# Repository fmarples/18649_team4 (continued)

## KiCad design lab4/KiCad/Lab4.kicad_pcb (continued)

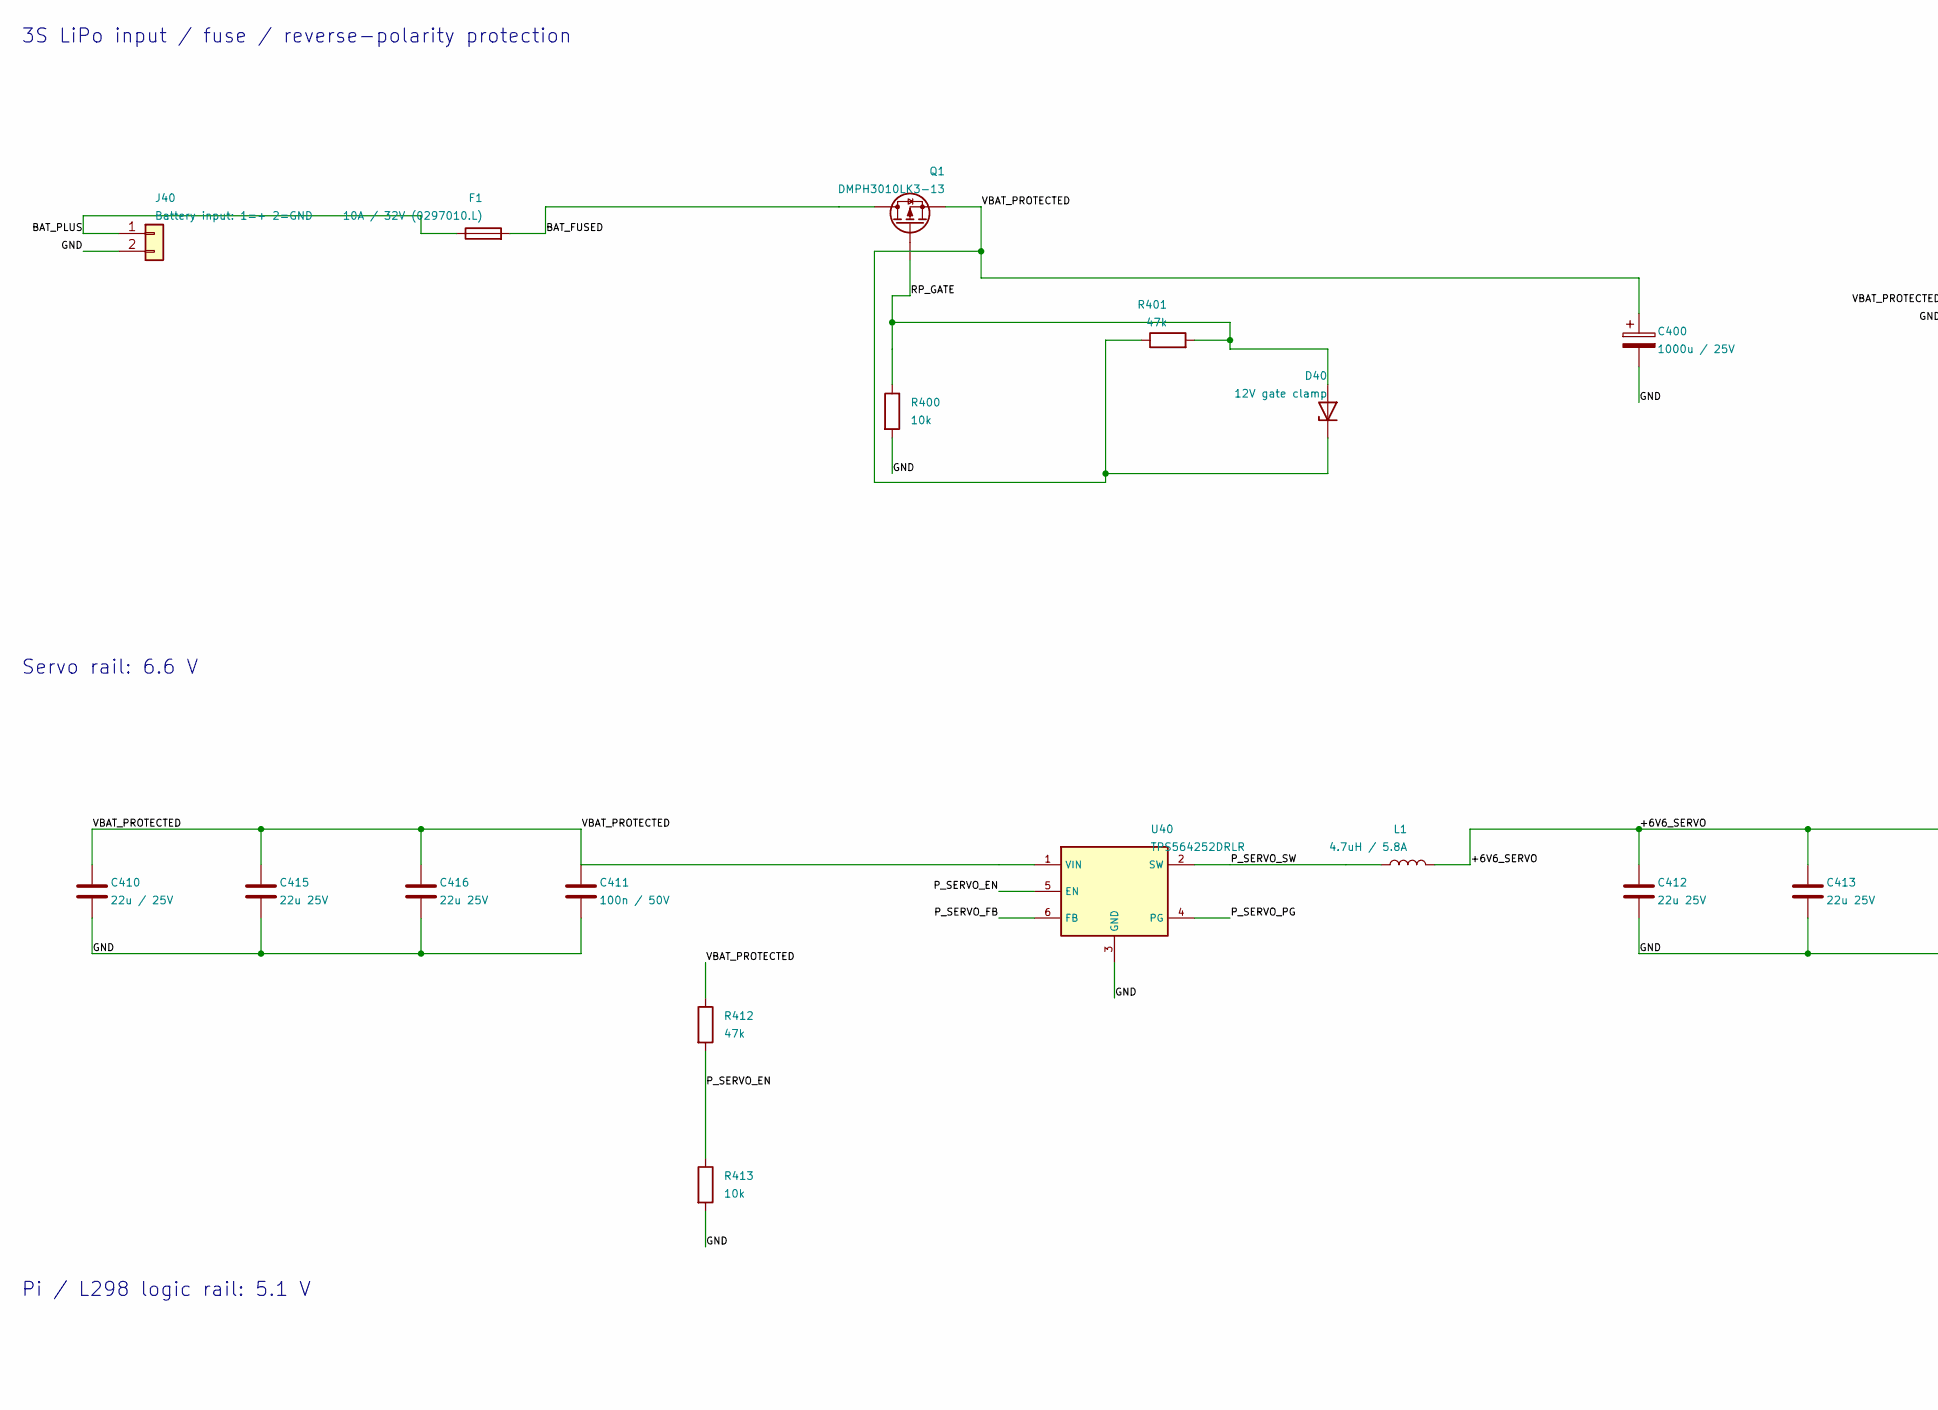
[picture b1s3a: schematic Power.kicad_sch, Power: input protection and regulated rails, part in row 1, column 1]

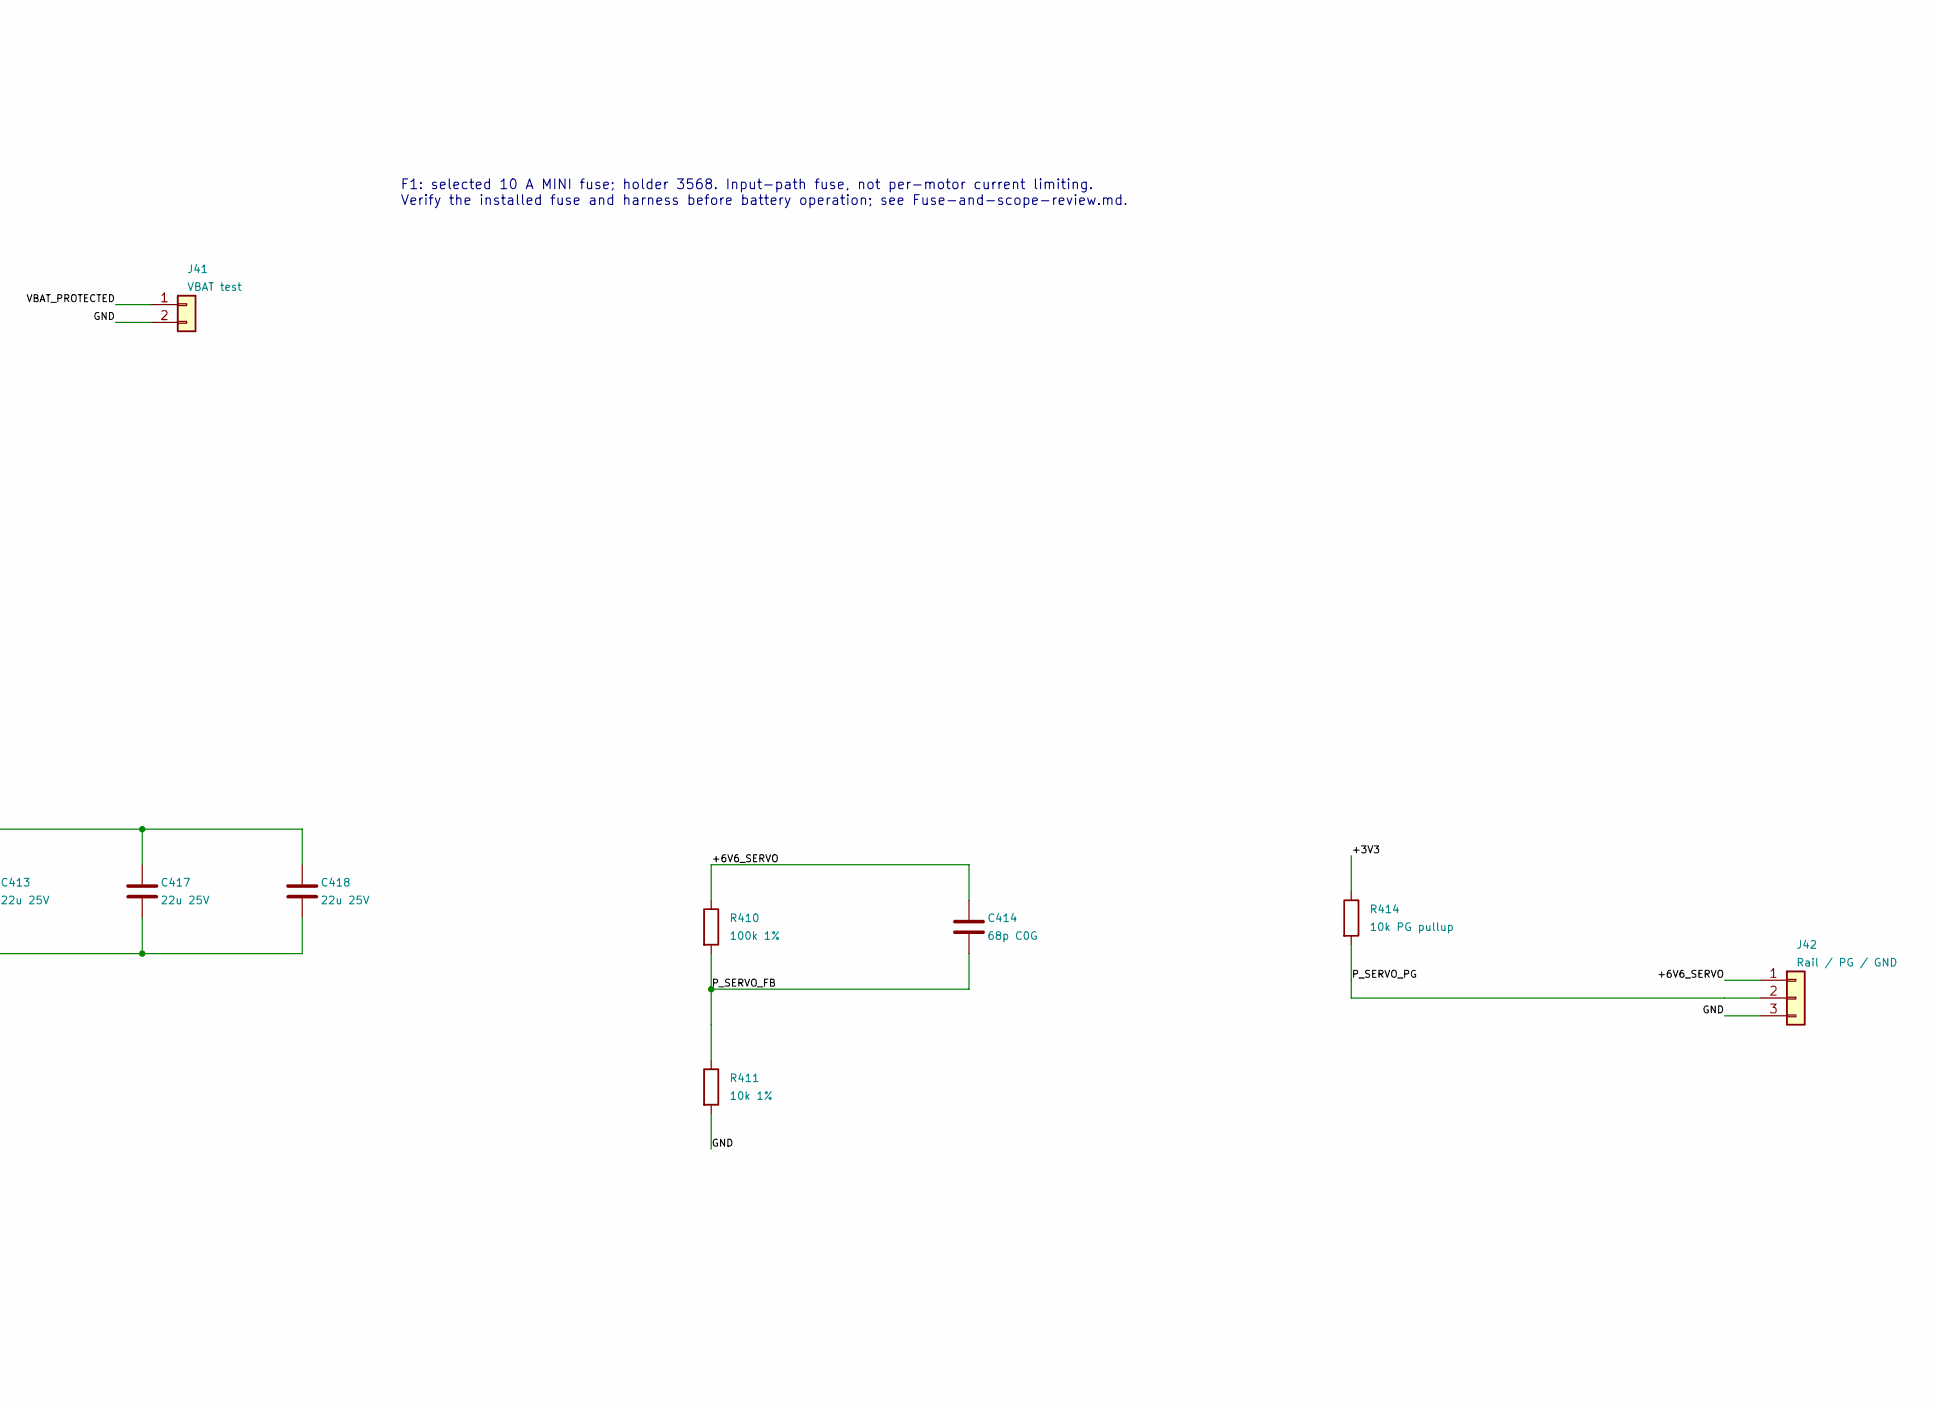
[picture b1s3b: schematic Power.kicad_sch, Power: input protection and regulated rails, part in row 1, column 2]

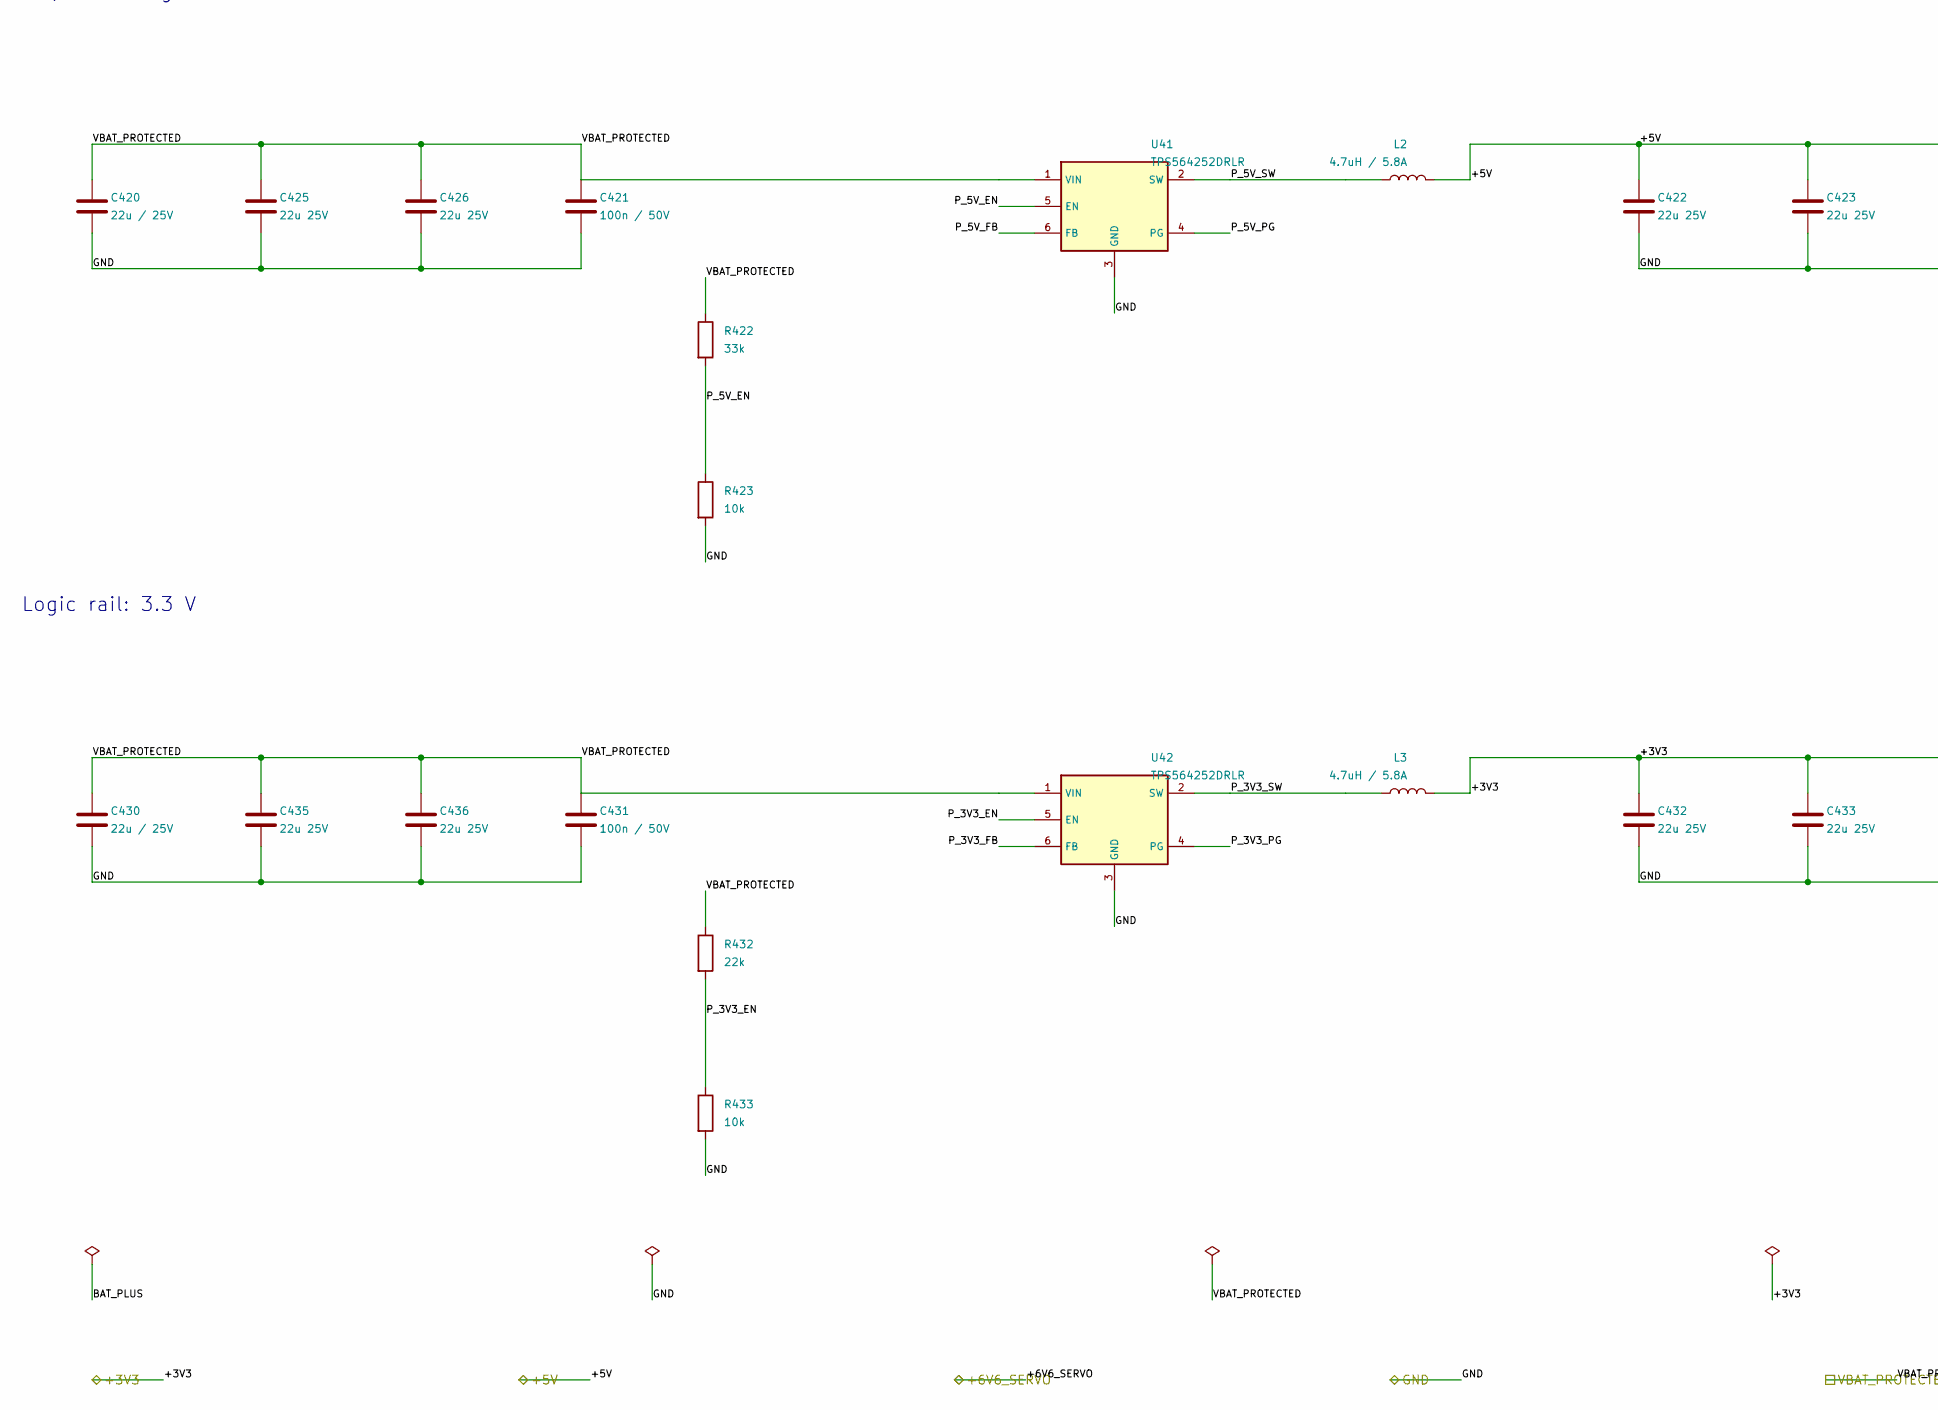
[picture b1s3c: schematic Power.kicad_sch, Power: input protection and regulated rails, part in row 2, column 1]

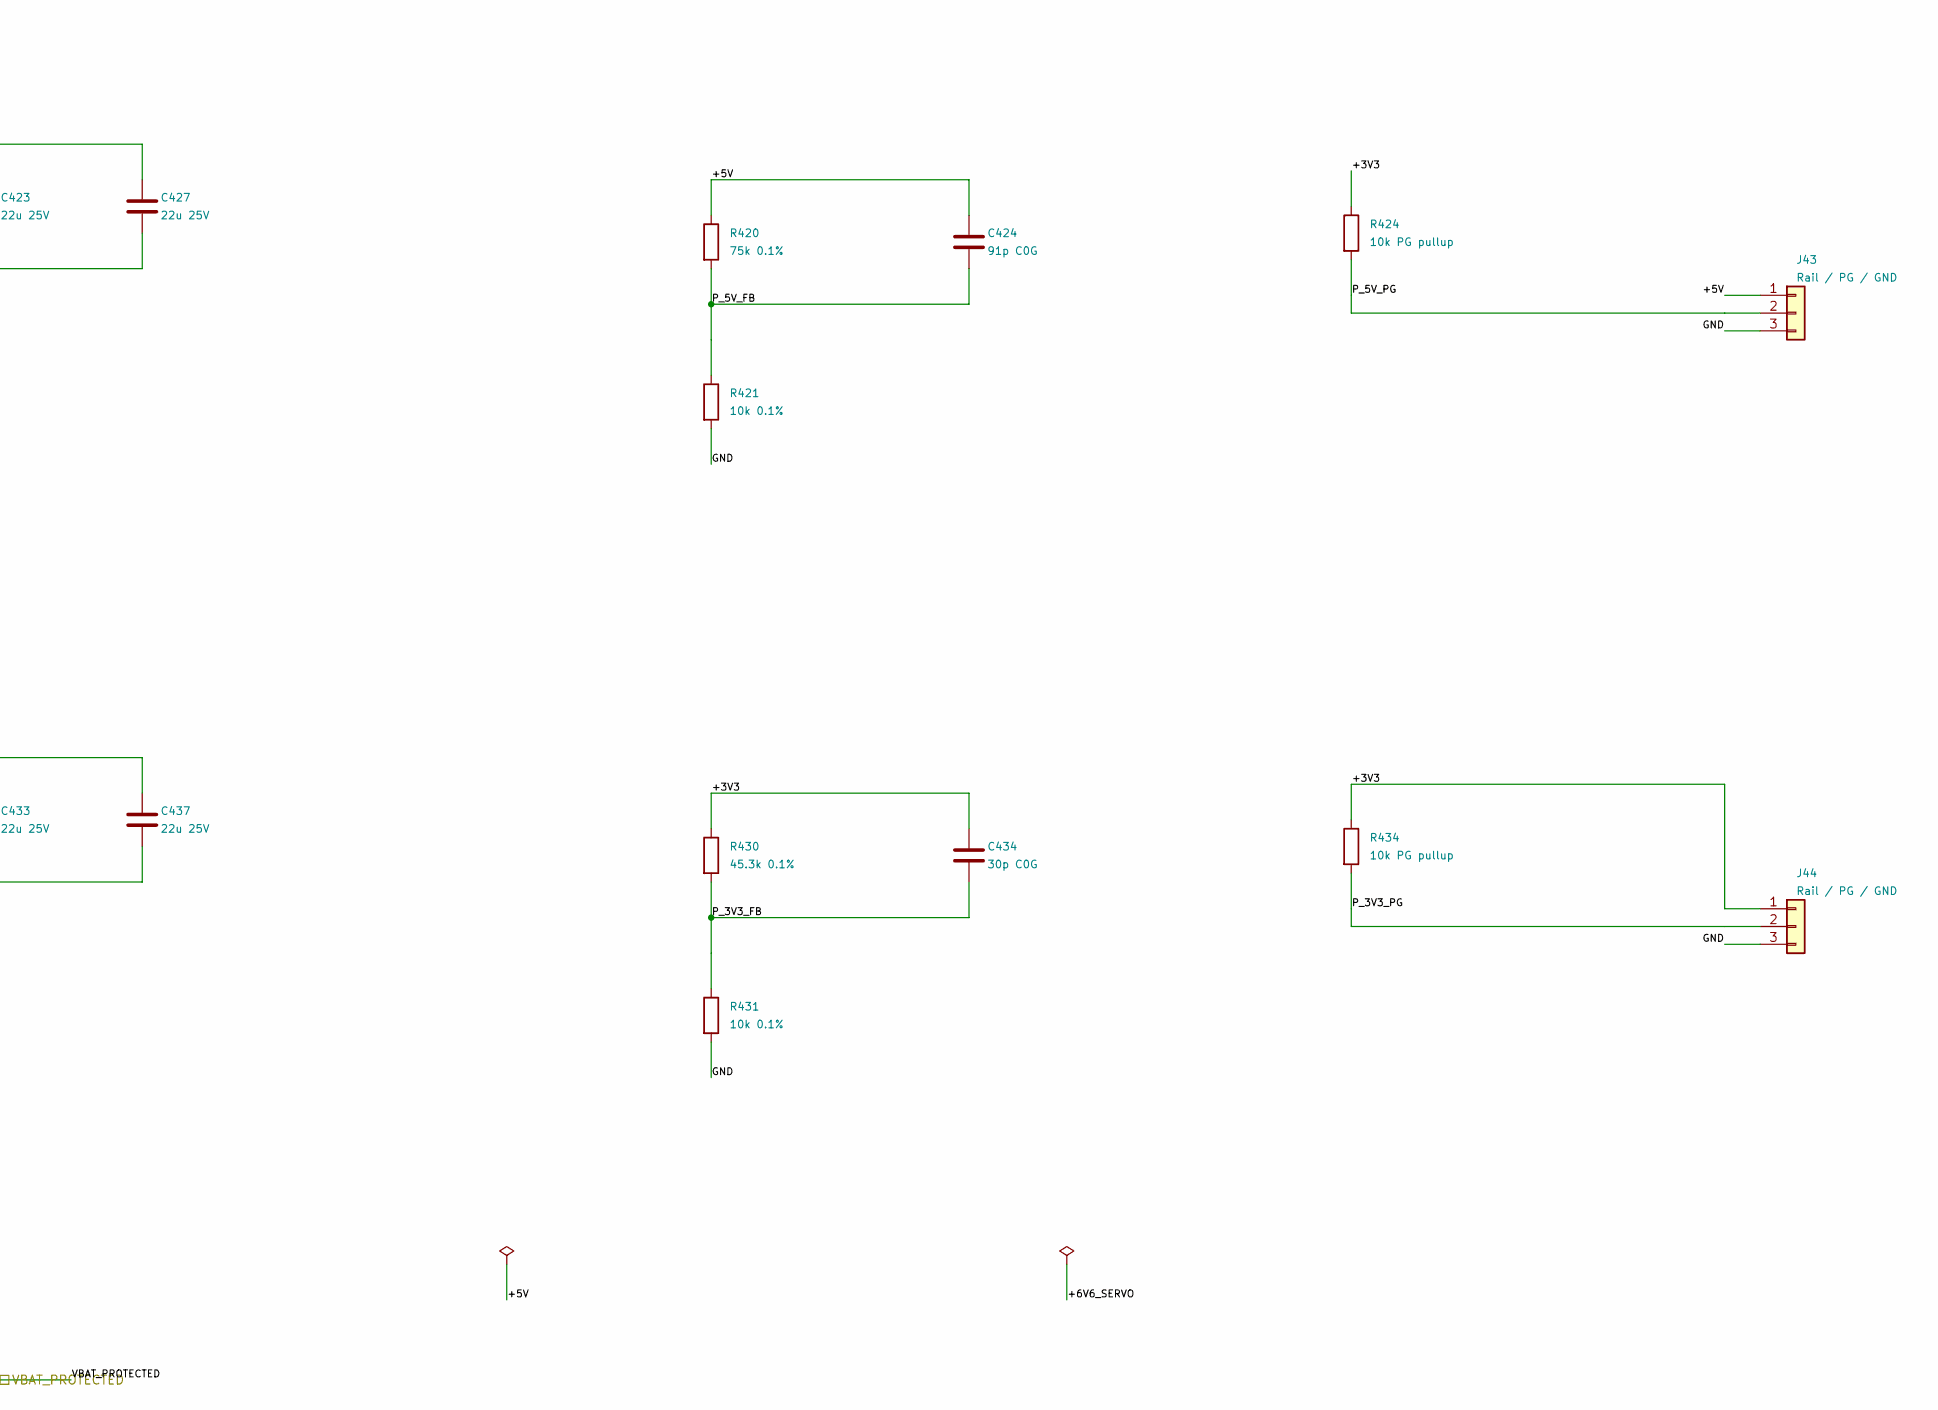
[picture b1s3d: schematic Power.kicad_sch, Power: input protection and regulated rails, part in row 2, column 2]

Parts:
C400: 1000u / 25V; CP_Radial_D12.5mm_P5.00mm; MPN UPW1E102MHD
C410, C420, C430: 22u / 25V; C_1210_3225Metric; MPN GRM32ER61E226KE15L
C411, C421, C431: 100n / 50V; C_0603_1608Metric; MPN GRM188R71H104KA93D
C412, C413, C415, C416, C417, C418, C422, C423, C425, C426, C427, C432, C433, C435, C436, C437: 22u 25V; C_1210_3225Metric; MPN GRM32ER61E226KE15L
C414: 68p C0G; C_0603_1608Metric; MPN GRM1885C1H680JA01D
C424: 91p C0G; C_0603_1608Metric; MPN GRM1885C1H910JA01D
C434: 30p C0G; C_0603_1608Metric; MPN GRM1885C1H300JA01D
D40: 12V gate clamp; D_SOD-123F; MPN BZT52C12
F1: 10A / 32V (0297010.L); Fuseholder_Blade_Mini_Keystone_3568; MPN 3568
J40: Battery input: 1=+ 2=GND; Hirose_DF63M-2P-3.96DSA_1x02_P3.96mm_Vertical; MPN DF63M-2P-3.96DSA
J41: VBAT test; PinHeader_1x02_P2.54mm_Vertical
J42, J43, J44: Rail / PG / GND; PinHeader_1x03_P2.54mm_Vertical
L1, L2, L3: 4.7uH / 5.8A; Eaton_SDCHA1V8040; MPN SDCHA1V8040-4R7-R
Q1: DMPH3010LK3-13; TO-252-2; MPN DMPH3010LK3-13
R400, R413, R423, R433: 10k; R_0603_1608Metric; MPN CRCW060310K0FKEA
R401, R412: 47k; R_0603_1608Metric; MPN RC0603FR-0747KL
R410: 100k 1%; R_0603_1608Metric; MPN RC0603FR-07100KL
R411: 10k 1%; R_0603_1608Metric; MPN CRCW060310K0FKEA
R414, R424, R434: 10k PG pullup; R_0603_1608Metric; MPN CRCW060310K0FKEA
R420: 75k 0.1%; R_0603_1608Metric; MPN RT0603BRD0775KL
R421, R431: 10k 0.1%; R_0603_1608Metric; MPN RT0603BRD0710KL
R422: 33k; R_0603_1608Metric; MPN RC0603FR-0733KL
R430: 45.3k 0.1%; R_0603_1608Metric; MPN RT0603BRD0745K3L
R432: 22k; R_0603_1608Metric; MPN RC0603FR-0722KL
U40, U41, U42: TPS564252DRLR; SOT-563; MPN TPS564252DRLR

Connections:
/+3V3: C432.1, C433.1, C434.1, C437.1, J44.1, L3.2, R414.1, R424.1, R430.1, R434.1; also elsewhere on the board
/+5V: C422.1, C423.1, C424.1, C427.1, J43.1, L2.2, R420.1; also elsewhere on the board
/+6V6_SERVO: C412.1, C413.1, C414.1, C417.1, C418.1, J42.1, L1.2, R410.1; also elsewhere on the board
/GND: C400.2, C410.2, C411.2, C412.2, C413.2, C415.2, C416.2, C417.2, C418.2, C420.2, C421.2, C422.2, C423.2, C425.2, C426.2, C427.2, C430.2, C431.2, C432.2, C433.2, C435.2, C436.2, C437.2, J40.2, J41.2, J42.3, J43.3, J44.3, R400.2, R411.2, R413.2, R421.2, R423.2, R431.2, R433.2, U40.3 (GND), U41.3 (GND), U42.3 (GND); also elsewhere on the board
/Power/BAT_FUSED: F1.2, Q1.2 (D)
/Power/BAT_PLUS: F1.1, J40.1
/Power/P_3V3_EN: R432.2, R433.1, U42.5 (EN)
/Power/P_3V3_FB: C434.2, R430.2, R431.1, U42.6 (FB)
/Power/P_3V3_PG: J44.2, R434.2, U42.4 (PG)
/Power/P_3V3_SW: L3.1, U42.2 (SW)
/Power/P_5V_EN: R422.2, R423.1, U41.5 (EN)
/Power/P_5V_FB: C424.2, R420.2, R421.1, U41.6 (FB)
/Power/P_5V_PG: J43.2, R424.2, U41.4 (PG)
/Power/P_5V_SW: L2.1, U41.2 (SW)
/Power/P_SERVO_EN: R412.2, R413.1, U40.5 (EN)
/Power/P_SERVO_FB: C414.2, R410.2, R411.1, U40.6 (FB)
/Power/P_SERVO_PG: J42.2, R414.2, U40.4 (PG)
/Power/P_SERVO_SW: L1.1, U40.2 (SW)
/Power/RP_GATE: D40.2 (A), Q1.1 (G), R400.1, R401.2
/VBAT_PROTECTED: C400.1, C410.1, C411.1, C415.1, C416.1, C420.1, C421.1, C425.1, C426.1, C430.1, C431.1, C435.1, C436.1, D40.1 (K), J41.1, Q1.3 (S), R401.1, R412.1, R422.1, R432.1, U40.1 (VIN), U41.1 (VIN), U42.1 (VIN); also elsewhere on the board

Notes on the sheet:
3S LiPo input / fuse / reverse-polarity protection
F1: selected 10 A MINI fuse; holder 3568. Input-path fuse, not per-motor current limiting. Verify the installed fuse and harness before battery operation; see Fuse-and-scope-review.md.
Servo rail: 6.6 V
Pi / L298 logic rail: 5.1 V
Logic rail: 3.3 V

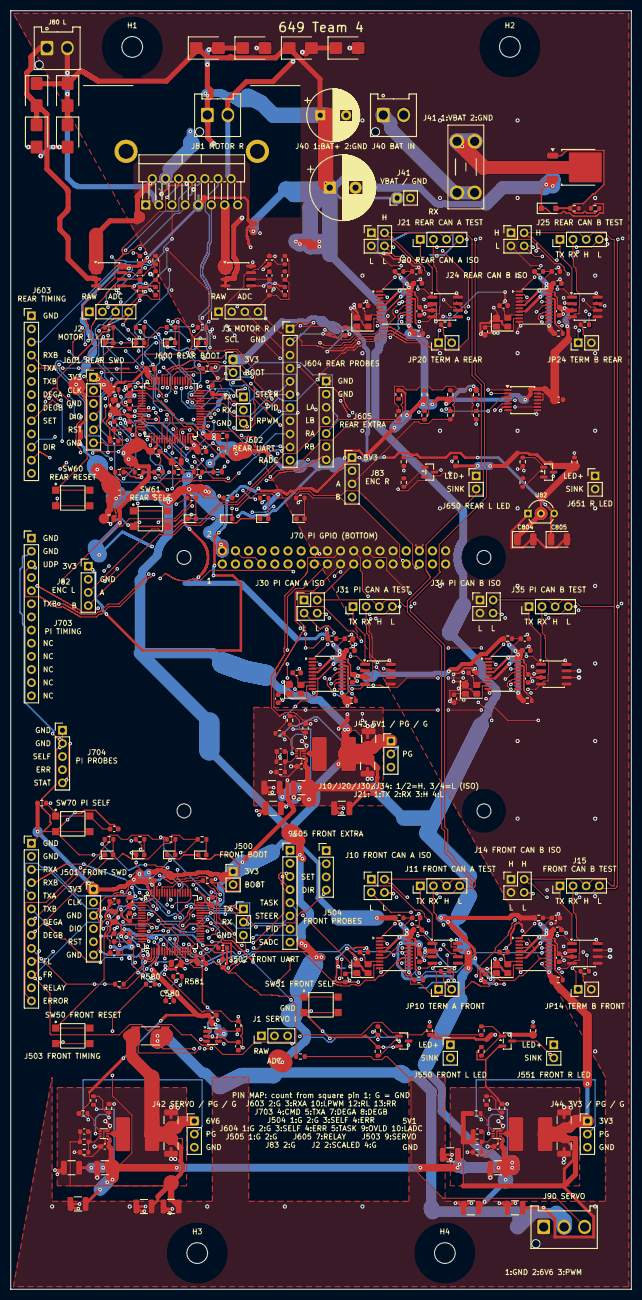
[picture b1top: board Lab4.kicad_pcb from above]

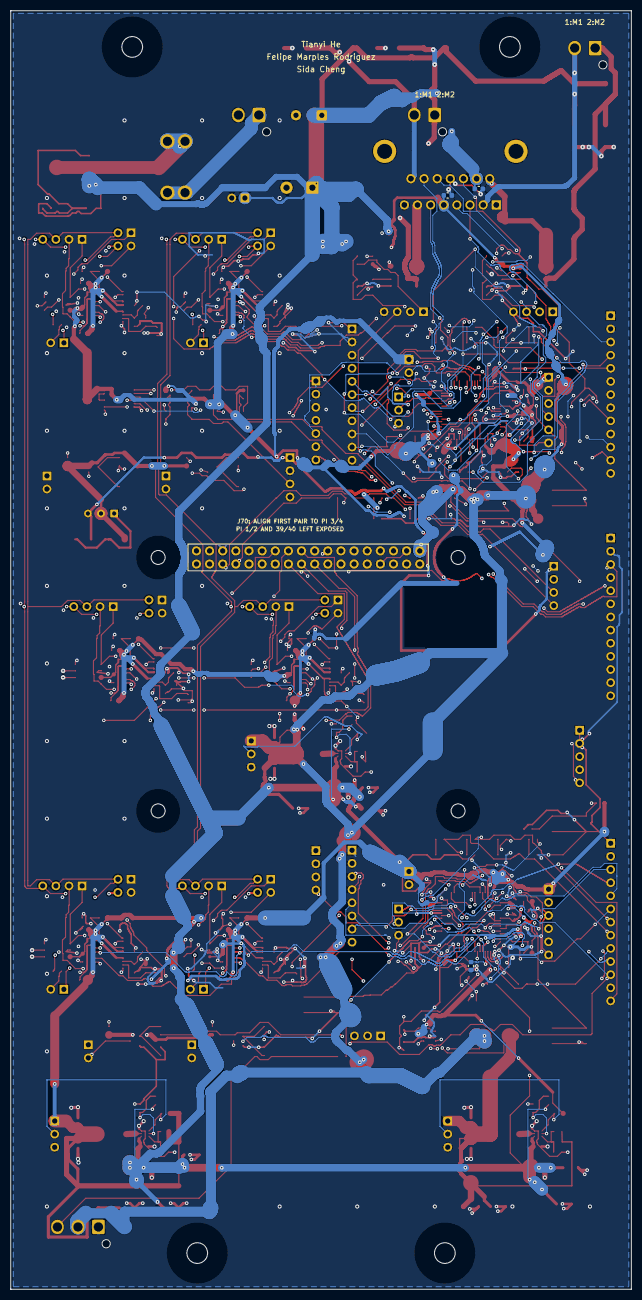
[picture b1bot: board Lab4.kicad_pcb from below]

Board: 4 copper layers, 120.0 x 247.2 mm, 309 parts (4 on the bottom side), 214 nets.

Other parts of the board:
H1, H2, H3, H4: M3 / 4.0mm clearance / 4mm exclusion; Chassis_support_M3_D4_4mm_edge
H5, H6, H7, H8: Pi support <=5.5mm hardware OD; Pi_support_M2.5_D5.5
HS80: 6396BG; Boyd_6396BG_StraightPins

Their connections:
/GND: HS80.MP1, HS80.MP2; also elsewhere on the board

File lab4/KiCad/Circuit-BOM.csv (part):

Sheet,Reference,Value,MPN,Footprint,Status
Front,U10,MCP2515T-I/ST,MCP2515T-I/ST,Package_SO:TSSOP-20_4.4x6.5mm_P0.65mm,Preliminary; verify before fabrication
Front,U11,SN65HVD231DR,SN65HVD231DR,Package_SO:SOIC-8_3.9x4.9mm_P1.27mm,Exact MPN appears in course v3 stock list; TI SOIC-8 pinout checked
Front,Y10,16 MHz,CX3225SB16000H0FLJCC,Crystal:Crystal_SMD_3225-4Pin_3.2x2.5mm,Load capacitor values require crystal CL and PCB stray capacitance
Front,C100,18p C0G 50V,GRM1885C1H180JA01D,Capacitor_SMD:C_0603_1608Metric,CL=12pF; equal 18pF caps assume 3pF effective stray; tune after layout/clock measurement
Front,C101,18p C0G 50V,GRM1885C1H180JA01D,Capacitor_SMD:C_0603_1608Metric,CL=12pF; equal 18pF caps assume 3pF effective stray; tune after layout/clock measurement
Front,R100,10k,CRCW060310K0FKEA,Resistor_SMD:R_0603_1608Metric,Preliminary; verify before fabrication
Front,C102,100n,KGM15AR71C104KT,Capacitor_SMD:C_0603_1608Metric,Preliminary; verify before fabrication
Front,R101,10k,CRCW060310K0FKEA,Resistor_SMD:R_0603_1608Metric,Preliminary; verify before fabrication
Front,C103,100n,KGM15AR71C104KT,Capacitor_SMD:C_0603_1608Metric,Preliminary; verify before fabrication
Front,C104,100n,KGM15AR71C104KT,Capacitor_SMD:C_0603_1608Metric,Preliminary; verify before fabrication
Front,J10,CAN A isolation,,Connector_PinHeader_2.54mm:PinHeader_2x02_P2.54mm_Vertical,Shunts 1-2 and 3-4; remove both to isolate this node
Front,J11,CAN A test,,Connector_PinHeader_2.54mm:PinHeader_1x04_P2.54mm_Vertical,Preliminary; verify before fabrication
Front,JP10,TERM A,,Connector_PinHeader_2.54mm:PinHeader_1x02_P2.54mm_Vertical,Preliminary; verify before fabrication
Front,R102,120R,RC0603FR-07120RL,Resistor_SMD:R_0603_1608Metric,Preliminary; verify before fabrication
Front,U14,MCP2515T-I/ST,MCP2515T-I/ST,Package_SO:TSSOP-20_4.4x6.5mm_P0.65mm,Preliminary; verify before fabrication
Front,U15,SN65HVD231DR,SN65HVD231DR,Package_SO:SOIC-8_3.9x4.9mm_P1.27mm,Exact MPN appears in course v3 stock list; TI SOIC-8 pinout checked
Front,Y14,16 MHz,CX3225SB16000H0FLJCC,Crystal:Crystal_SMD_3225-4Pin_3.2x2.5mm,Load capacitor values require crystal CL and PCB stray capacitance
Front,C140,18p C0G 50V,GRM1885C1H180JA01D,Capacitor_SMD:C_0603_1608Metric,CL=12pF; equal 18pF caps assume 3pF effective stray; tune after layout/clock measurement
Front,C141,18p C0G 50V,GRM1885C1H180JA01D,Capacitor_SMD:C_0603_1608Metric,CL=12pF; equal 18pF caps assume 3pF effective stray; tune after layout/clock measurement
Front,R140,10k,CRCW060310K0FKEA,Resistor_SMD:R_0603_1608Metric,Preliminary; verify before fabrication
Front,C142,100n,KGM15AR71C104KT,Capacitor_SMD:C_0603_1608Metric,Preliminary; verify before fabrication
Front,R141,10k,CRCW060310K0FKEA,Resistor_SMD:R_0603_1608Metric,Preliminary; verify before fabrication
Front,C143,100n,KGM15AR71C104KT,Capacitor_SMD:C_0603_1608Metric,Preliminary; verify before fabrication
Front,C144,100n,KGM15AR71C104KT,Capacitor_SMD:C_0603_1608Metric,Preliminary; verify before fabrication
Front,J14,CAN B isolation,,Connector_PinHeader_2.54mm:PinHeader_2x02_P2.54mm_Vertical,Shunts 1-2 and 3-4; remove both to isolate this node
Front,J15,CAN B test,,Connector_PinHeader_2.54mm:PinHeader_1x04_P2.54mm_Vertical,Preliminary; verify before fabrication
Front,JP14,TERM B,,Connector_PinHeader_2.54mm:PinHeader_1x02_P2.54mm_Vertical,Preliminary; verify before fabrication
Front,R142,120R,RC0603FR-07120RL,Resistor_SMD:R_0603_1608Metric,Preliminary; verify before fabrication
Rear,U20,MCP2515T-I/ST,MCP2515T-I/ST,Package_SO:TSSOP-20_4.4x6.5mm_P0.65mm,Preliminary; verify before fabrication
Rear,U21,SN65HVD231DR,SN65HVD231DR,Package_SO:SOIC-8_3.9x4.9mm_P1.27mm,Exact MPN appears in course v3 stock list; TI SOIC-8 pinout checked
Rear,Y20,16 MHz,CX3225SB16000H0FLJCC,Crystal:Crystal_SMD_3225-4Pin_3.2x2.5mm,Load capacitor values require crystal CL and PCB stray capacitance
Rear,C200,18p C0G 50V,GRM1885C1H180JA01D,Capacitor_SMD:C_0603_1608Metric,CL=12pF; equal 18pF caps assume 3pF effective stray; tune after layout/clock measurement
Rear,C201,18p C0G 50V,GRM1885C1H180JA01D,Capacitor_SMD:C_0603_1608Metric,CL=12pF; equal 18pF caps assume 3pF effective stray; tune after layout/clock measurement
Rear,R200,10k,CRCW060310K0FKEA,Resistor_SMD:R_0603_1608Metric,Preliminary; verify before fabrication
Rear,C202,100n,KGM15AR71C104KT,Capacitor_SMD:C_0603_1608Metric,Preliminary; verify before fabrication
Rear,R201,10k,CRCW060310K0FKEA,Resistor_SMD:R_0603_1608Metric,Preliminary; verify before fabrication
Rear,C203,100n,KGM15AR71C104KT,Capacitor_SMD:C_0603_1608Metric,Preliminary; verify before fabrication
Rear,C204,100n,KGM15AR71C104KT,Capacitor_SMD:C_0603_1608Metric,Preliminary; verify before fabrication
Rear,J20,CAN A isolation,,Connector_PinHeader_2.54mm:PinHeader_2x02_P2.54mm_Vertical,Shunts 1-2 and 3-4; remove both to isolate this node
Rear,J21,CAN A test,,Connector_PinHeader_2.54mm:PinHeader_1x04_P2.54mm_Vertical,Preliminary; verify before fabrication
Rear,JP20,TERM A,,Connector_PinHeader_2.54mm:PinHeader_1x02_P2.54mm_Vertical,Preliminary; verify before fabrication
Rear,R202,120R,RC0603FR-07120RL,Resistor_SMD:R_0603_1608Metric,Preliminary; verify before fabrication
Rear,U24,MCP2515T-I/ST,MCP2515T-I/ST,Package_SO:TSSOP-20_4.4x6.5mm_P0.65mm,Preliminary; verify before fabrication
Rear,U25,SN65HVD231DR,SN65HVD231DR,Package_SO:SOIC-8_3.9x4.9mm_P1.27mm,Exact MPN appears in course v3 stock list; TI SOIC-8 pinout checked
Rear,Y24,16 MHz,CX3225SB16000H0FLJCC,Crystal:Crystal_SMD_3225-4Pin_3.2x2.5mm,Load capacitor values require crystal CL and PCB stray capacitance
Rear,C240,18p C0G 50V,GRM1885C1H180JA01D,Capacitor_SMD:C_0603_1608Metric,CL=12pF; equal 18pF caps assume 3pF effective stray; tune after layout/clock measurement
Rear,C241,18p C0G 50V,GRM1885C1H180JA01D,Capacitor_SMD:C_0603_1608Metric,CL=12pF; equal 18pF caps assume 3pF effective stray; tune after layout/clock measurement
Rear,R240,10k,CRCW060310K0FKEA,Resistor_SMD:R_0603_1608Metric,Preliminary; verify before fabrication
Rear,C242,100n,KGM15AR71C104KT,Capacitor_SMD:C_0603_1608Metric,Preliminary; verify before fabrication
Rear,R241,10k,CRCW060310K0FKEA,Resistor_SMD:R_0603_1608Metric,Preliminary; verify before fabrication
Rear,C243,100n,KGM15AR71C104KT,Capacitor_SMD:C_0603_1608Metric,Preliminary; verify before fabrication
Rear,C244,100n,KGM15AR71C104KT,Capacitor_SMD:C_0603_1608Metric,Preliminary; verify before fabrication
Rear,J24,CAN B isolation,,Connector_PinHeader_2.54mm:PinHeader_2x02_P2.54mm_Vertical,Shunts 1-2 and 3-4; remove both to isolate this node
Rear,J25,CAN B test,,Connector_PinHeader_2.54mm:PinHeader_1x04_P2.54mm_Vertical,Preliminary; verify before fabrication
Rear,JP24,TERM B,,Connector_PinHeader_2.54mm:PinHeader_1x02_P2.54mm_Vertical,Preliminary; verify before fabrication
Rear,R242,120R,RC0603FR-07120RL,Resistor_SMD:R_0603_1608Metric,Preliminary; verify before fabrication
Cockpit,U30,MCP2515T-I/ST,MCP2515T-I/ST,Package_SO:TSSOP-20_4.4x6.5mm_P0.65mm,Preliminary; verify before fabrication
Cockpit,U31,SN65HVD231DR,SN65HVD231DR,Package_SO:SOIC-8_3.9x4.9mm_P1.27mm,Exact MPN appears in course v3 stock list; TI SOIC-8 pinout checked
Cockpit,Y30,16 MHz,CX3225SB16000H0FLJCC,Crystal:Crystal_SMD_3225-4Pin_3.2x2.5mm,Load capacitor values require crystal CL and PCB stray capacitance
Cockpit,C300,18p C0G 50V,GRM1885C1H180JA01D,Capacitor_SMD:C_0603_1608Metric,CL=12pF; equal 18pF caps assume 3pF effective stray; tune after layout/clock measurement
Cockpit,C301,18p C0G 50V,GRM1885C1H180JA01D,Capacitor_SMD:C_0603_1608Metric,CL=12pF; equal 18pF caps assume 3pF effective stray; tune after layout/clock measurement
Cockpit,R300,10k,CRCW060310K0FKEA,Resistor_SMD:R_0603_1608Metric,Preliminary; verify before fabrication
Cockpit,C302,100n,KGM15AR71C104KT,Capacitor_SMD:C_0603_1608Metric,Preliminary; verify before fabrication
Cockpit,R301,10k,CRCW060310K0FKEA,Resistor_SMD:R_0603_1608Metric,Preliminary; verify before fabrication
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
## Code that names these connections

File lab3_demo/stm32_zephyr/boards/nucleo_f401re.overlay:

/* Lab 3 Part 5 demo, shared by N2 and N3. Pin record: doc/LAB3_PINOUT.md.
 * CAN modules: SPI1 PA5/PA6/PA7 (XIAO D8 SCK, D9 MISO, D10 MOSI per the
 * handout erratum); module A CS PB6 / INT PA10, module B CS PC7 / INT PB5.
 * CONFIG_LAB3_SWAP_CAN_AB maps logical bus A to module B for a board whose
 * modules are wired to the opposite physical buses.
 */
#include <zephyr/dt-bindings/gpio/gpio.h>
#include <zephyr/dt-bindings/pwm/pwm.h>

/ {
    aliases { can-a = &can_a; can-b = &can_b; };
    zephyr,user {
        can-rx-a-gpios = <&gpioc 2 GPIO_ACTIVE_HIGH>;
        can-rx-b-gpios = <&gpioc 3 GPIO_ACTIVE_HIGH>;
        can-tx-a-gpios = <&gpioa 0 GPIO_ACTIVE_HIGH>;
        can-tx-b-gpios = <&gpioa 1 GPIO_ACTIVE_HIGH>;
        degraded-a-gpios = <&gpiob 0 GPIO_ACTIVE_HIGH>;
        degraded-b-gpios = <&gpiob 1 GPIO_ACTIVE_HIGH>;
        error-gpios = <&gpioc 0 GPIO_ACTIVE_HIGH>;
        /* STEER task-body marker; the SRV test point is the PB4 PWM below. */
        steer-task-gpios = <&gpioc 1 GPIO_ACTIVE_HIGH>;
        pwm-set-gpios = <&gpiob 9 GPIO_ACTIVE_HIGH>;
        dir-a-gpios = <&gpiob 10 GPIO_ACTIVE_HIGH>;
        /* PB11 does not exist on the LQFP64 package (pin 30 is VCAP1). */
        pid-gpios = <&gpioc 9 GPIO_ACTIVE_HIGH>;
        relay-tx-gpios = <&gpioc 6 GPIO_ACTIVE_HIGH>;
        front-left-gpios = <&gpioa 4 GPIO_ACTIVE_HIGH>;
        front-right-gpios = <&gpiob 8 GPIO_ACTIVE_HIGH>;
        rear-left-gpios = <&gpioc 4 GPIO_ACTIVE_HIGH>;
        rear-right-gpios = <&gpioc 5 GPIO_ACTIVE_HIGH>;
        test-button-gpios = <&gpioc 13 GPIO_ACTIVE_LOW>; /* built-in blue B1 */
        task-probe-gpios = <&gpioc 8 GPIO_ACTIVE_HIGH>;
        /* PB4/D5 TIM3_CH1: SRV servo pulse on N2, PWM_OUT motor PWM on N3.
         * Each zone passes its own period at run time. */
        pwms = <&pwm3 1 PWM_MSEC(20) PWM_POLARITY_NORMAL>;
    };
};

&spi1 {
    status = "okay";
    pinctrl-0 = <&spi1_sck_pa5 &spi1_miso_pa6 &spi1_mosi_pa7>;
    pinctrl-names = "default";
    cs-gpios = <&gpiob 6 (GPIO_ACTIVE_LOW | GPIO_PULL_UP)>,
               <&gpioc 7 (GPIO_ACTIVE_LOW | GPIO_PULL_UP)>;
    can_a: mcp2515@0 {
        compatible = "microchip,mcp2515";
        reg = <0>;
        spi-max-frequency = <10000000>; /* MCP2515 max; SPI1 runs 84 MHz/16 = 5.25 MHz */
        int-gpios = <&gpioa 10 GPIO_ACTIVE_LOW>;
        osc-freq = <16000000>;
        status = "okay";
    };
    can_b: mcp2515@1 {
        compatible = "microchip,mcp2515";
        reg = <1>;
        spi-max-frequency = <10000000>;
        int-gpios = <&gpiob 5 GPIO_ACTIVE_LOW>;
        osc-freq = <16000000>;
        status = "okay";
    };
};

/* 84 MHz / (83 + 1) = 1 us ticks: 20000 per servo period, 100 per 10 kHz motor period. */
&timers3 {
    status = "okay";
    st,prescaler = <83>;
    pwm3: pwm {
        status = "okay";
        pinctrl-0 = <&tim3_ch1_pb4>;
        pinctrl-names = "default";
    };
};

/* Board defaults that claim Lab 3 pins: USART1 PB6 (CAN A CS), I2C1 PB8/PB9
 * (FR LED, PWM_SET), I2C3 PA8/PC9 (PID marker), TIM2 PWM PA5 (SPI SCK). */
&usart1 { status = "disabled"; };
&i2c1 { status = "disabled"; };
&i2c3 { status = "disabled"; };
&timers2 { status = "disabled"; };

&iwdg { status = "okay"; };

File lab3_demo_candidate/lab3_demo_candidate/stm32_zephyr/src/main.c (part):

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    rc = wdt_setup(watchdog_dev, 0);
    if (rc != 0) { printk("IWDG setup failed: %d\n", rc); return rc; }
    printk("%s Lab 3 demo online. CAN A/B at 500 kbit/s; outputs are GPIO/LED only.\n", APP_NAME);
    printk("Trace: RX_A=PC2 RX_B=PC3 TX_A=PA0 TX_B=PA1 DEG_A=PB0 DEG_B=PB1 ERR=PC0.\n");
    while (true) { apply_blink_outputs(); k_msleep(2); }
}

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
